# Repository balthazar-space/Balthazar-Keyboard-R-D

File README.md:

# Balthazar

Open-hardware laptop computer modules description and concept.

These are electronic schematic modules as presented at https://balthazar.space/wiki/Balthazar with the main aim for team access. See the [main repository](https://github.com/balthazar-space/balthazar) for other designs.

# Balthazar Keyboard
Keyboard and touchpad module - computer keyboard system with microcontroller (for now an 8-bit Atmel built into a small Sparkfun ProMicro board). A normal ISO keyboard layout is used. 

An option is given to test the ability of the microcontroller to handle also the control for PSU board and the touchpad module data transfer to USB. Keypad and touchpad user activities are usually mutually exclusive – so this seems ok. Charger control is active a couple of seconds on startup of the system, so this is also ok. 

In case of some charger error there is a mechanical switch on PSU board to stop charging. In this way three functions would be fulfilled in a single microcontroller – connected to the system IO with one USB.

Keyboard pcb has some dimensions already defined by the LCD's dimensions of 13.3 inch in diagonal: 290mm x 180mm. The width is the most determining factor for the keys raster which is about 17mm – instead of the regular 19mm. 

The keys have some ergonomic solution that gives some additional design touch.  

The keyboard switches are important but are for now very typical low cost membrane switches. A little better solution are the softer (silicone) – but still membrane – switches. The idea is to have a waterproof (silicone) layer over the whole board. The board can then already act as a top cover. The feel of silicone rubber is preferred to that of natural rubber. 

However, this is not finite, and we are pusing to try to deliver the best option.

KiCad files are in version 5.1.5 format.

## License

All resources except the keyboard firmware - which is licensed with with GPLv3 or later - licensed under the CERN Open Hardware Licence CERN-OHL W V.2.0

Version 2.0 of the CERN-OHL introduces three variants of the licence – strongly (S) reciprocal, weakly (W) reciprocal and permissive (P) – which aim to address specific constraints caused by different collaboration models currently used in open-hardware projects. 

The first two variants mean that if any product is made using an open hardware design, the design of that product, including any improvements or modifications, should be made available under the same licence as that of the original product. Permissive licences do not impose this condition.

See the [LICENSE.md](./LICENSE.md) file for more information.

## Funding

This project is funded through the [NGI Zero Entrust Fund](https://nlnet.nl/entrust), a fund
established by [NLnet](https://nlnet.nl) with financial support from the European Commission's
[Next Generation Internet](https://ngi.eu) program. Learn more on the [NLnet project page](https://nlnet.nl/project/Balthazar-Casing/).

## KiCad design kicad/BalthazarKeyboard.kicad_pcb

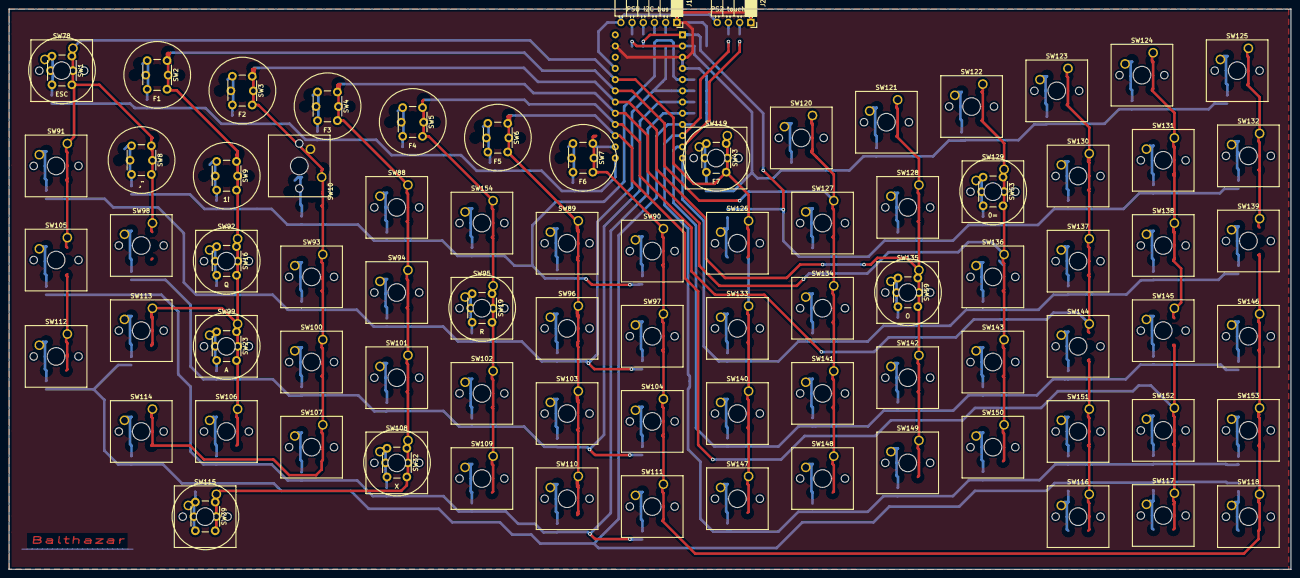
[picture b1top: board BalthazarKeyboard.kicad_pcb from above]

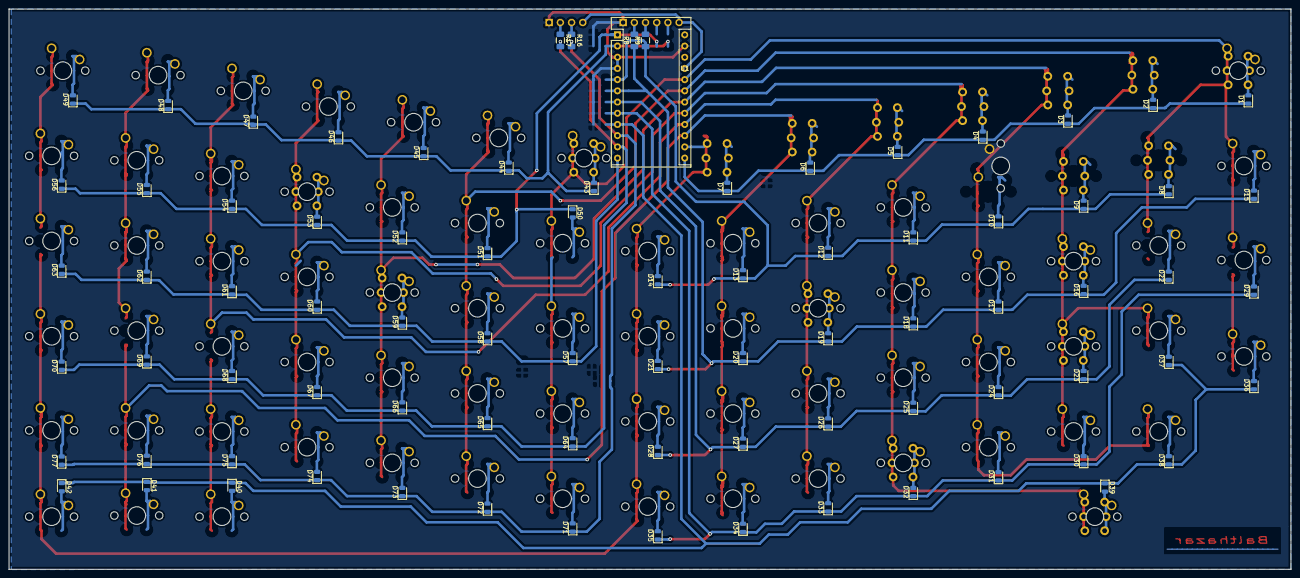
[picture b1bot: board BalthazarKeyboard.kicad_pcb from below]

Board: 2 copper layers, 290.6 x 127.0 mm, 170 parts (82 on the bottom side), 101 nets.

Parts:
D1, D2, D3, D4, D5, D6, D7, D8, D9, D10, D11, D12, D13, D14, D15, D16, D17, D18, D19, D20, D21, D22, D23, D24, D25, D26, D27, D28, D29, D30, D31, D32, D33, D34, D35, D36, D37, D38, D39, D40, D41, D42, D43, D44, D45, D46, D47, D48, D49, D50, D51, D52, D53, D54, D55, D56, D57, D58, D59, D60, D61, D62, D63, D64, D65, D66, D67, D68, D69, D70, D71, D72, D73, D74, D75, D76, D77: D; D_0805_2012Metric
J1: PSU I2C bus; PinSocket_1x06_P2.54mm_Horizontal
J2: PS2 touchpad; PinSocket_1x04_P2.54mm_Horizontal
R8, R9, R16, R17: 200; R_1206_3216Metric
SW1: ESC; SW_PUSH_6mm_8mm
SW2: F1; SW_PUSH_6mm_8mm
SW3: F2; SW_PUSH_6mm_8mm
SW4: F3; SW_PUSH_6mm_8mm
SW5: F4; SW_PUSH_6mm_8mm
SW6: F5; SW_PUSH_6mm_8mm
SW7: F6; SW_PUSH_6mm_8mm
SW8: ¸¨; SW_PUSH_6mm_8mm
SW9: 1!; SW_PUSH_6mm_8mm
SW10: 2; SW_PUSH_6mm_8mm
SW16: Q; SW_PUSH_6mm_8mm
SW19: R; SW_PUSH_6mm_8mm
SW23: A; SW_PUSH_6mm_8mm
SW32: X; SW_PUSH_6mm_8mm
SW39: SPACE; SW_PUSH_6mm_8mm
SW43: F7; SW_PUSH_6mm_8mm
SW53: 0=; SW_PUSH_6mm_8mm
SW59: O; SW_PUSH_6mm_8mm
SW78: ESC; SW_Cherry_MX_1.00u_PCB
SW88: 3#; SW_Cherry_MX_1.00u_PCB
SW89: 5%; SW_Cherry_MX_1.00u_PCB
SW90: 6&; SW_Cherry_MX_1.00u_PCB
SW91: TAB; SW_Cherry_MX_1.00u_PCB
SW92: Q; SW_Cherry_MX_1.00u_PCB
SW93: W; SW_Cherry_MX_1.00u_PCB
SW94: E; SW_Cherry_MX_1.00u_PCB
SW95: R; SW_Cherry_MX_1.00u_PCB
SW96: T; SW_Cherry_MX_1.00u_PCB
SW97, SW107: Y/Z; SW_Cherry_MX_1.00u_PCB
SW98: CAPS; SW_Cherry_MX_1.00u_PCB
SW99: A; SW_Cherry_MX_1.00u_PCB
SW100: S; SW_Cherry_MX_1.00u_PCB
SW101: D; SW_Cherry_MX_1.00u_PCB
SW102: F; SW_Cherry_MX_1.00u_PCB
SW103: G; SW_Cherry_MX_1.00u_PCB
SW104: H; SW_Cherry_MX_1.00u_PCB
SW105, SW153: SHIFT; SW_Cherry_MX_1.00u_PCB
SW106: <>; SW_Cherry_MX_1.00u_PCB
SW108: X; SW_Cherry_MX_1.00u_PCB
SW109: C; SW_Cherry_MX_1.00u_PCB
SW110: V; SW_Cherry_MX_1.00u_PCB
SW111: B; SW_Cherry_MX_1.00u_PCB
SW112: CTRL; SW_Cherry_MX_1.00u_PCB
SW113: ALT; SW_Cherry_MX_1.00u_PCB
SW114: Win/Apple; SW_Cherry_MX_1.00u_PCB
SW115: SPACE; SW_Cherry_MX_1.00u_PCB
SW116: LEFT; SW_Cherry_MX_1.00u_PCB
SW117: DOWN; SW_Cherry_MX_1.00u_PCB
SW118: RIGHT; SW_Cherry_MX_1.00u_PCB
SW119: F7; SW_Cherry_MX_1.00u_PCB
SW120: F8; SW_Cherry_MX_1.00u_PCB
SW121: F9; SW_Cherry_MX_1.00u_PCB
SW122: F10; SW_Cherry_MX_1.00u_PCB
SW123: F11; SW_Cherry_MX_1.00u_PCB
SW124: F12; SW_Cherry_MX_1.00u_PCB
SW125: F13 PRTSCR; SW_Cherry_MX_1.00u_PCB
SW126: 7/; SW_Cherry_MX_1.00u_PCB
SW127: 8(; SW_Cherry_MX_1.00u_PCB
SW128: 9); SW_Cherry_MX_1.00u_PCB
SW129: 0=; SW_Cherry_MX_1.00u_PCB
SW130: /?; SW_Cherry_MX_1.00u_PCB
SW131: +*; SW_Cherry_MX_1.00u_PCB
SW132: DELETE; SW_Cherry_MX_1.00u_PCB
SW133: U; SW_Cherry_MX_1.00u_PCB
SW134: I; SW_Cherry_MX_1.00u_PCB
SW135: O; SW_Cherry_MX_1.00u_PCB
SW136: P; SW_Cherry_MX_1.00u_PCB
SW137: Š; SW_Cherry_MX_1.00u_PCB
SW138: Đ; SW_Cherry_MX_1.00u_PCB
SW139: BACKSPACE; SW_Cherry_MX_1.00u_PCB
SW140: J; SW_Cherry_MX_1.00u_PCB
SW141: K; SW_Cherry_MX_1.00u_PCB
SW142: L; SW_Cherry_MX_1.00u_PCB
SW143: Č; SW_Cherry_MX_1.00u_PCB
SW144: Ć; SW_Cherry_MX_1.00u_PCB
SW145: Ž; SW_Cherry_MX_1.00u_PCB
SW146: ENTER; SW_Cherry_MX_1.00u_PCB
SW147: N; SW_Cherry_MX_1.00u_PCB
SW148: M; SW_Cherry_MX_1.00u_PCB
SW149: ,;; SW_Cherry_MX_1.00u_PCB
SW150: .:; SW_Cherry_MX_1.00u_PCB
SW151: -_; SW_Cherry_MX_1.00u_PCB
SW152: UP; SW_Cherry_MX_1.00u_PCB
SW154: 4$; SW_Cherry_MX_1.00u_PCB
U1: Pro Micro; Arduino_ProMicro

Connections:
GND: J1.1, J2.1, U1.3, U1.4, U1.23
unnamed: D1.2, SW1.2, SW78.2
unnamed: D2.2, SW2.2
unnamed: D3.2, SW3.2
unnamed: D4.2, SW4.2
unnamed: D5.2, SW5.2
unnamed: D6.2, SW6.2
unnamed: D7.2, SW7.2
unnamed: D8.2, SW8.2
unnamed: D9.2, SW9.2
unnamed: D10.2, SW10.2
unnamed: D11.2, SW88.2
unnamed: D12.2, SW154.2
unnamed: D13.2, SW89.2
unnamed: D14.2, SW90.2
unnamed: D15.2, SW91.2
unnamed: D16.2, SW16.2, SW92.2
unnamed: D17.2, SW93.2
unnamed: D18.2, SW94.2
unnamed: D19.2, SW19.2, SW95.2
unnamed: D20.2, SW96.2
unnamed: D21.2, SW97.2
unnamed: D22.2, SW98.2
unnamed: D23.2, SW23.2, SW99.2
unnamed: D24.2, SW100.2
unnamed: D25.2, SW101.2
unnamed: D26.2, SW102.2
unnamed: D27.2, SW103.2
unnamed: D28.2, SW104.2
unnamed: D29.2, SW105.2
unnamed: D30.2, SW106.2
unnamed: D31.2, SW107.2
unnamed: D32.2, SW32.2, SW108.2
unnamed: D33.2, SW109.2
unnamed: D34.2, SW110.2
unnamed: D35.2, SW111.2
unnamed: D36.2, SW112.2
unnamed: D37.2, SW113.2
unnamed: D38.2, SW114.2
unnamed: D39.2, SW39.2, SW115.2
unnamed: D40.2, SW116.2
unnamed: D41.2, SW117.2
unnamed: D42.2, SW118.2
unnamed: D43.2, SW43.2, SW119.2
unnamed: D44.2, SW120.2
unnamed: D45.2, SW121.2
unnamed: D46.2, SW122.2
unnamed: D47.2, SW123.2
unnamed: D48.2, SW124.2
unnamed: D49.2, SW125.2
unnamed: D50.2, SW126.2
unnamed: D51.2, SW127.2
unnamed: D52.2, SW128.2
unnamed: D53.2, SW53.2, SW129.2
unnamed: D54.2, SW130.2
unnamed: D55.2, SW131.2
unnamed: D56.2, SW132.2
unnamed: D57.2, SW133.2
unnamed: D58.2, SW134.2
unnamed: D59.2, SW59.2, SW135.2
unnamed: D60.2, SW136.2
unnamed: D61.2, SW137.2
unnamed: D62.2, SW138.2
unnamed: D63.2, SW139.2
unnamed: D64.2, SW140.2
unnamed: D65.2, SW141.2
unnamed: D66.2, SW142.2
unnamed: D67.2, SW143.2
unnamed: D68.2, SW144.2
unnamed: D69.2, SW145.2
unnamed: D70.2, SW146.2
unnamed: D71.2, SW147.2
unnamed: D72.2, SW148.2
unnamed: D73.2, SW149.2
unnamed: D74.2, SW150.2
unnamed: D75.2, SW151.2
unnamed: D76.2, SW152.2
unnamed: D77.2, SW153.2
unnamed: J1.2, R8.2
unnamed: J1.3, R9.2
unnamed: J1.6, J2.4, U1.21
unnamed: J2.2, R17.1
unnamed: J2.3, R16.1
col1: D1.1, D2.1, D3.1, D4.1, D5.1, D6.1, D7.1, U1.13
col2: D8.1, D9.1, D10.1, D11.1, D12.1, D13.1, D14.1, R9.1, U1.5
col3: D15.1, D16.1, D17.1, D18.1, D19.1, D20.1, D21.1, R8.1, U1.6
col4: D22.1, D23.1, D24.1, D25.1, D26.1, D27.1, D28.1, U1.7
col5: D29.1, D30.1, D31.1, D32.1, D33.1, D34.1, D35.1, U1.8
col6: D36.1, D37.1, D38.1, D39.1, D40.1, D41.1, D42.1, U1.9
col7: D71.1, D72.1, D73.1, D74.1, D75.1, D76.1, D77.1, R16.2, U1.10
col8: D64.1, D65.1, D66.1, D67.1, D68.1, D69.1, D70.1, R17.2, U1.11
col9: D57.1, D58.1, D59.1, D60.1, D61.1, D62.1, D63.1, U1.12
col10: D50.1, D51.1, D52.1, D53.1, D54.1, D55.1, D56.1, U1.1
col11: D43.1, D44.1, D45.1, D46.1, D47.1, D48.1, D49.1, U1.2
row1: SW1.1, SW8.1, SW43.1, SW78.1, SW91.1, SW98.1, SW105.1, SW112.1, SW119.1, SW126.1, SW133.1, SW140.1, SW147.1, U1.20
row2: SW2.1, SW9.1, SW16.1, SW23.1, SW92.1, SW99.1, SW106.1, SW113.1, SW120.1, SW127.1, SW134.1, SW141.1, SW148.1, U1.19
row3: SW3.1, SW10.1, SW59.1, SW93.1, SW100.1, SW107.1, SW114.1, SW121.1, SW128.1, SW135.1, SW142.1, SW149.1, U1.18
row4: SW4.1, SW32.1, SW39.1, SW53.1, SW88.1, SW94.1, SW101.1, SW108.1, SW115.1, SW122.1, SW129.1, SW136.1, SW143.1, SW150.1, U1.17
row5: SW5.1, SW19.1, SW95.1, SW102.1, SW109.1, SW116.1, SW123.1, SW130.1, SW137.1, SW144.1, SW151.1, SW154.1, U1.16
row6: SW6.1, SW89.1, SW96.1, SW103.1, SW110.1, SW117.1, SW124.1, SW131.1, SW138.1, SW145.1, SW152.1, U1.15
row7: SW7.1, SW90.1, SW97.1, SW104.1, SW111.1, SW118.1, SW125.1, SW132.1, SW139.1, SW146.1, SW153.1, U1.14

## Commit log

2020-05-19 Create LICENSE
2020-06-19 NGI0-FSFE: Updating license file to include full license text
2021-07-28 admin
